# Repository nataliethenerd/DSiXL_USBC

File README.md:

## DSi XL USB C
Adds USB C charging with CC resistors for C to C charging.

| Item | Link |
| ---- | ---- |
| USB C Port | [Link](https://www.aliexpress.com/item/1005007105117672.html) |
| 2x 5.1K 0402 Resistors | [Link](https://s.click.aliexpress.com/e/_c3PvT58V) |

### 3D printed parts
They arent perfect, feel free to edit it if you can do better and please share them for everyone else :)

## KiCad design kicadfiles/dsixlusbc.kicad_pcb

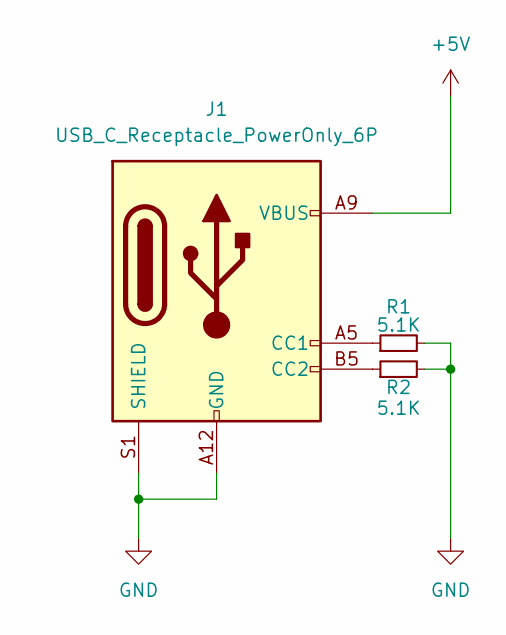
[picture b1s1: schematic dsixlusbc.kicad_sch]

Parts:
J1: USB_C_Receptacle_PowerOnly_6P; USB_C_Receptacle_GCT_USB4135-GF-A_6P_TopMnt_Horizontal
R1, R2: 5.1K; R_0402_1005Metric

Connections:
+5V: J1.A9 (VBUS), J1.B9 (VBUS)
GND: J1.A12 (GND), J1.B12 (GND), J1.S1 (SHIELD), R1.2, R2.2
unnamed: J1.A5 (CC1), R1.1
unnamed: J1.B5 (CC2), R2.1

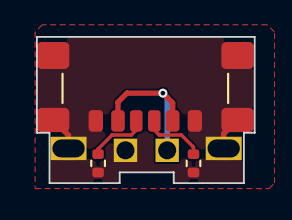
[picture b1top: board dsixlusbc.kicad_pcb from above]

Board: 4 copper layers, 12.1 x 8.1 mm, 3 parts (0 on the bottom side), 4 nets.

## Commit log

2026-06-07 first
